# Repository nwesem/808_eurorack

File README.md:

# 808_eurorack
808 eurorack kicad

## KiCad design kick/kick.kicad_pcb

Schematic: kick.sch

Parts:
C1, C2, C4, C5, C8: 100n
C3, C6, C7: 15n
C9, C10, C12: 0.47/50
C11: 33/6.3
C13: 220p
D1: 1N914A
D2, D3: 1N4148
J1, J3: TRIGGER IN
J2: EURO_PWR_2x5
Q1, Q2, Q4, Q5, Q6: BC546
Q3: BC556
R1, R10, R12, R24, R27: 100k
R2: 8.2k
R3, R9, R21: 22k
R4, R7, R19: 10k
R5: 2.7k
R6, R11: 4.7k
R8, R13, R14: 1M
R15, R25: 6.8k
R16, R20, R22: 47k
R17: 220
R18: 470k
R23: 82k
R26: 1k
RV1, RV2: 10k
RV3: 500kB
U1: TL072P

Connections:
+12V: C5.1, Q3.3, Q6.2, R6.1, R8.1, R9.1, U1.8; also elsewhere on the board
-12V: C4.2, U1.4; also elsewhere on the board
GND: C2.1, C4.1, C5.2, C8.1, C13.1, D2.2, D3.1, J1.2, J3.2, Q1.3, Q2.3, Q4.3, Q5.3, R1.2, R4.2, R5.2, R11.2, R16.2, R21.2, R24.2, R25.2, R27.2, RV2.3; also elsewhere on the board
unnamed: C1.1, R3.1
unnamed: C1.2, D1.1, R1.1
unnamed: C2.2, Q2.2, Q4.1, R8.2
unnamed: C3.1, D2.1, R10.1, R11.1, U1.3
unnamed: C3.2, Q3.2, R2.2, R10.2
unnamed: C6.1, C7.2, R13.1, R15.1, R18.2
unnamed: C6.2, R14.2, U1.2
unnamed: C7.1, R14.1, R17.1, R20.2, U1.1
unnamed: C8.2, C9.2, R19.2, RV1.2, RV1.3
unnamed: C9.1, RV2.1
unnamed: C10.1, RV2.2
unnamed: C10.2, R23.2
unnamed: C11.1, RV3.3
unnamed: C11.2, R18.1, R22.1, U1.7
unnamed: C12.1, C13.2, Q6.3, R25.1
unnamed: C12.2, R26.2, R27.1
unnamed: D1.2, J1.1
unnamed: D3.2, Q4.2, R9.2, R12.2, R13.2
unnamed: J3.1, R26.1
unnamed: Q1.1, R3.2, R4.1
unnamed: Q1.2, R7.2
unnamed: Q2.1, R2.1, R5.1
unnamed: Q3.1, R6.2, R7.1
unnamed: Q5.1, R12.1
unnamed: Q5.2, R15.2, R16.1
unnamed: Q6.1, R23.1, R24.1
unnamed: R17.2, R19.1, RV1.1
unnamed: R20.1, R22.2, RV3.1, RV3.2, U1.6
unnamed: R21.1, U1.5

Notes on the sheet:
TONE
ACCENT tie to +12V?

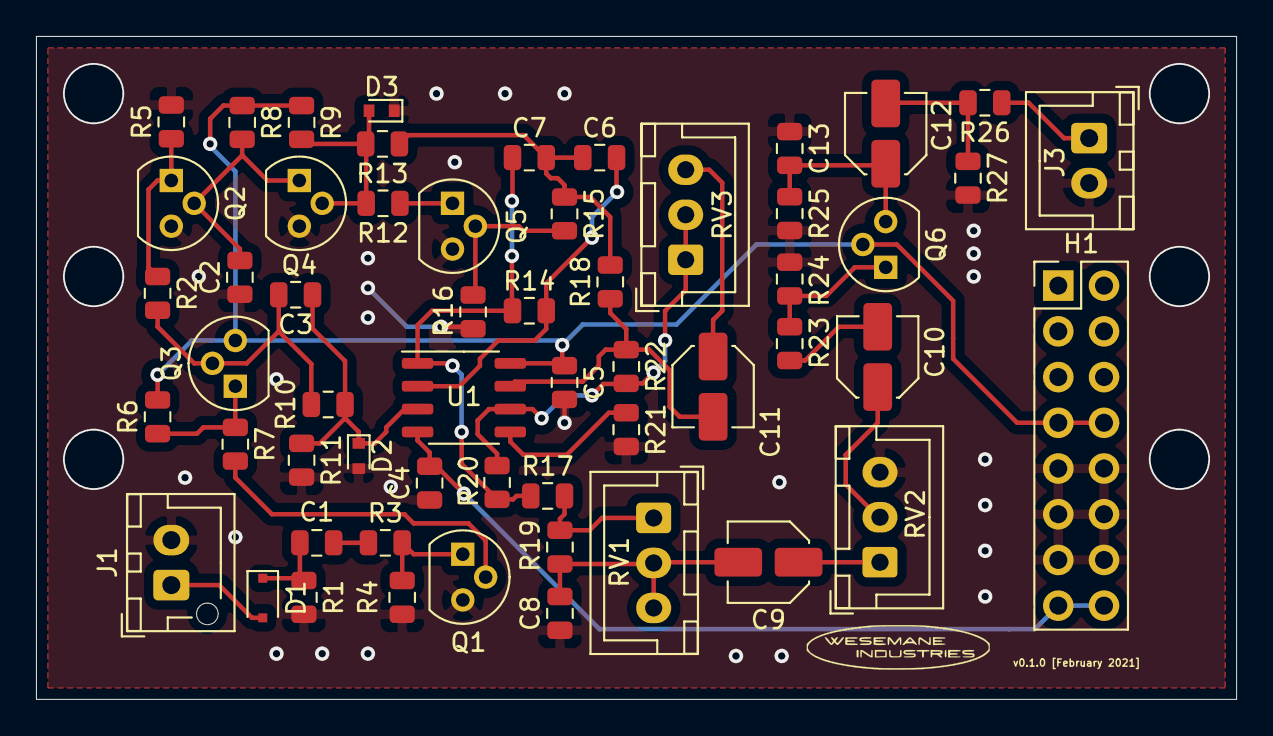
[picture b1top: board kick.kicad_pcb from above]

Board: 2 copper layers, 66.7 x 36.8 mm, 56 parts (0 on the bottom side), 32 nets.

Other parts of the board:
H1: PIN_HEADER_2x8; PinHeader_2x08_P2.54mm_Vertical

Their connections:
+12V: H1.7, H1.8; also elsewhere on the board
-12V: H1.15, H1.16; also elsewhere on the board
GND: H1.9, H1.10, H1.11, H1.12, H1.13, H1.14; also elsewhere on the board

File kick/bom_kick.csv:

"Id";"Designator";"Package";"Quantity";"Designation";"Supplier and ref";
1;"R6,R11";"R_0805_2012Metric";2;"4.7k";;;
2;"C1,C2,C4,C5,C8";"C_0805_2012Metric";5;"100n";;;
3;"C3,C6,C7";"C_0805_2012Metric";3;"15n";;;
4;"C9,C10,C12";"C_Elec_4x5.4";3;"0.47/50";;;
5;"C11";"C_Elec_4x5.4";1;"33/6.3";;;
6;"C13";"C_0805_2012Metric";1;"220p";;;
7;"D1";"D_SOD-323F";1;"1N914A";;;
8;"D2,D3";"D_SOD-523";2;"1N4148";;;
9;"H1";"PinHeader_2x08_P2.54mm_Vertical";1;"PIN_HEADER_2x8";;;
10;"J1";"JST_XH_B2B-XH-AM_1x02_P2.50mm_Vertical";1;"CV IN";;;
11;"J3";"JST_XH_B2B-XH-A_1x02_P2.50mm_Vertical";1;"TRIGGER OUT";;;
12;"Q1,Q2,Q4,Q5,Q6";"TO-92";5;"BC546";;;
13;"Q3";"TO-92";1;"BC556";;;
14;"R1,R10,R12,R24,R27";"R_0805_2012Metric";5;"100k";;;
15;"R2";"R_0805_2012Metric";1;"8.2k";;;
16;"R3,R9,R21";"R_0805_2012Metric";3;"22k";;;
17;"R4,R7,R19";"R_0805_2012Metric";3;"10k";;;
18;"R5";"R_0805_2012Metric";1;"2.7k";;;
19;"R8,R13,R14";"R_0805_2012Metric";3;"1M";;;
20;"R15,R25";"R_0805_2012Metric";2;"6.8k";;;
21;"R16,R20,R22";"R_0805_2012Metric";3;"47k";;;
22;"R17";"R_0805_2012Metric";1;"220";;;
23;"R18";"R_0805_2012Metric";1;"470k";;;
24;"R23";"R_0805_2012Metric";1;"82k";;;
25;"R26";"R_0805_2012Metric";1;"1k";;;
26;"RV1,RV2";"JST_XH_B3B-XH-A_1x03_P2.50mm_Vertical";2;"10k";;;
27;"RV3";"JST_XH_B3B-XH-A_1x03_P2.50mm_Vertical";1;"500kB";;;
28;"U1";"SO-8_3.9x4.9mm_P1.27mm";1;"TL072P";;;

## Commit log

2019-02-15 schematic for kick done, working hihats
2020-09-13 started layout for kick
2021-02-24 add pcb layout
2021-02-25 finished kick layout and ordered pcb
